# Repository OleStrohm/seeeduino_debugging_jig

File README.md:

# Seeeduino debugging jig

A debugging jig made for the Seeeduino Xiao family of boards.
This jig snaps onto the board and allows the Raspberry pi pico to communicate via the pins on the bottom of the board.

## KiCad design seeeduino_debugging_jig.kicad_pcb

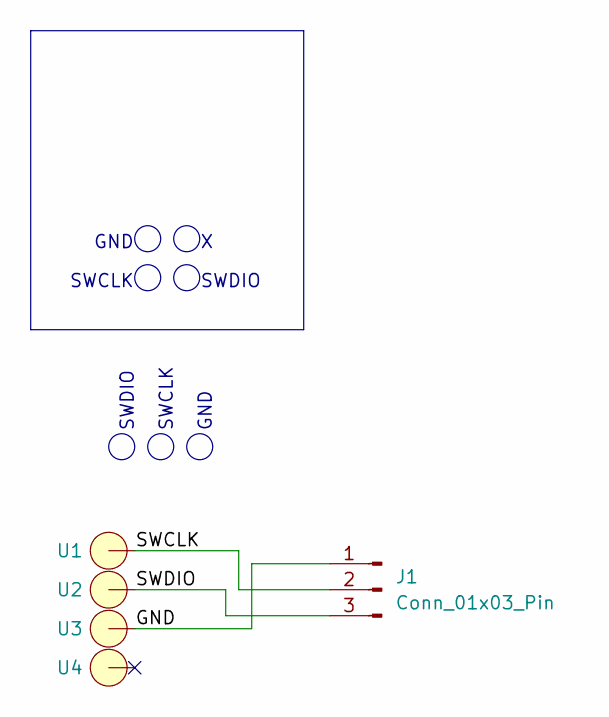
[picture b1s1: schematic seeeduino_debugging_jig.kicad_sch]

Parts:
J1: Conn_01x03_Pin; edge_connector
U1, U2, U3, U4: Pogo Pin

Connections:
/GND: J1.1, U3.1
/SWCLK: J1.2, U1.1
/SWDIO: J1.3, U2.1

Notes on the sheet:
SWDIO
GND
SWCLK

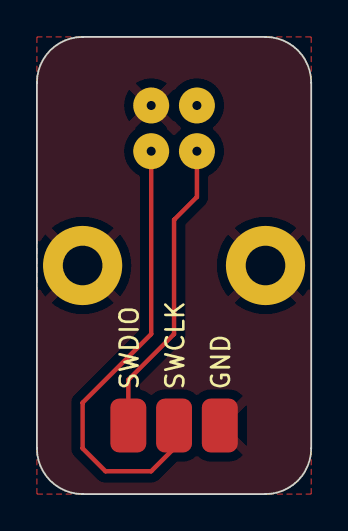
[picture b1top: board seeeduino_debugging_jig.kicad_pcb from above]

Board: 2 copper layers, 15.2 x 25.4 mm, 5 parts (0 on the bottom side), 3 nets.

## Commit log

2024-04-16 Completed v1.0
2024-04-17 Add a KiCanvas badge
2024-09-21 Created holder 3D model
2024-09-21 Exported 3D model
2024-09-21 Export STL model
2024-09-21 Add slot for USB-C cable
2024-09-21 Reduced size of catch
2024-09-21 Actually updated freecad file
2024-09-22 Add another catch at the bottom and improve the hole attachments
2024-09-22 Actually export the model
